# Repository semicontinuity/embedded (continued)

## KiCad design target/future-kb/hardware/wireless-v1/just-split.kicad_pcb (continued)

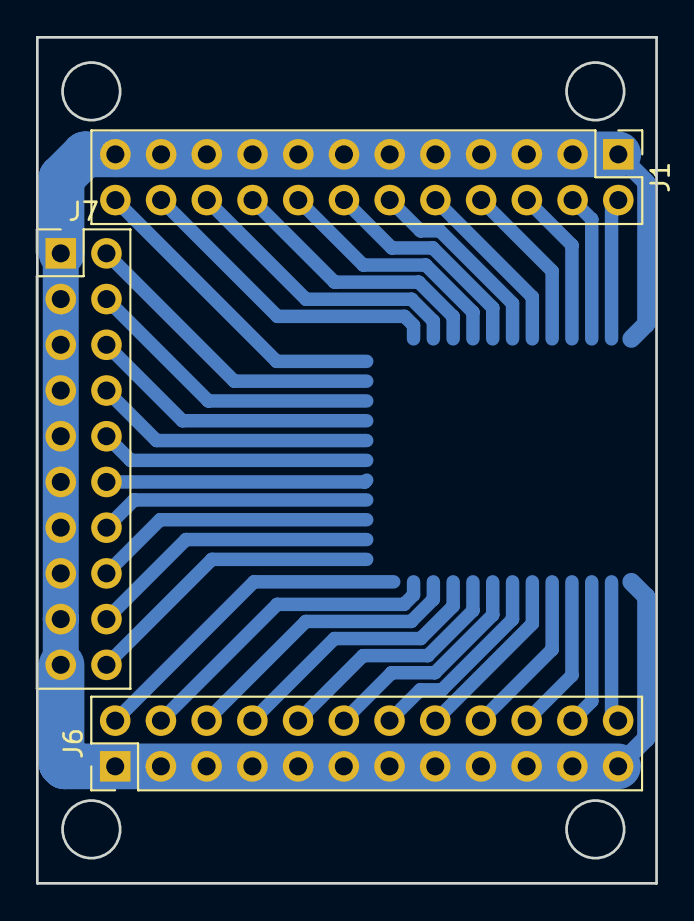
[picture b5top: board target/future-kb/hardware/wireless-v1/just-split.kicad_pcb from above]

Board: 2 copper layers, 34.4 x 47.0 mm, 4 parts (1 on the bottom side), 35 nets.

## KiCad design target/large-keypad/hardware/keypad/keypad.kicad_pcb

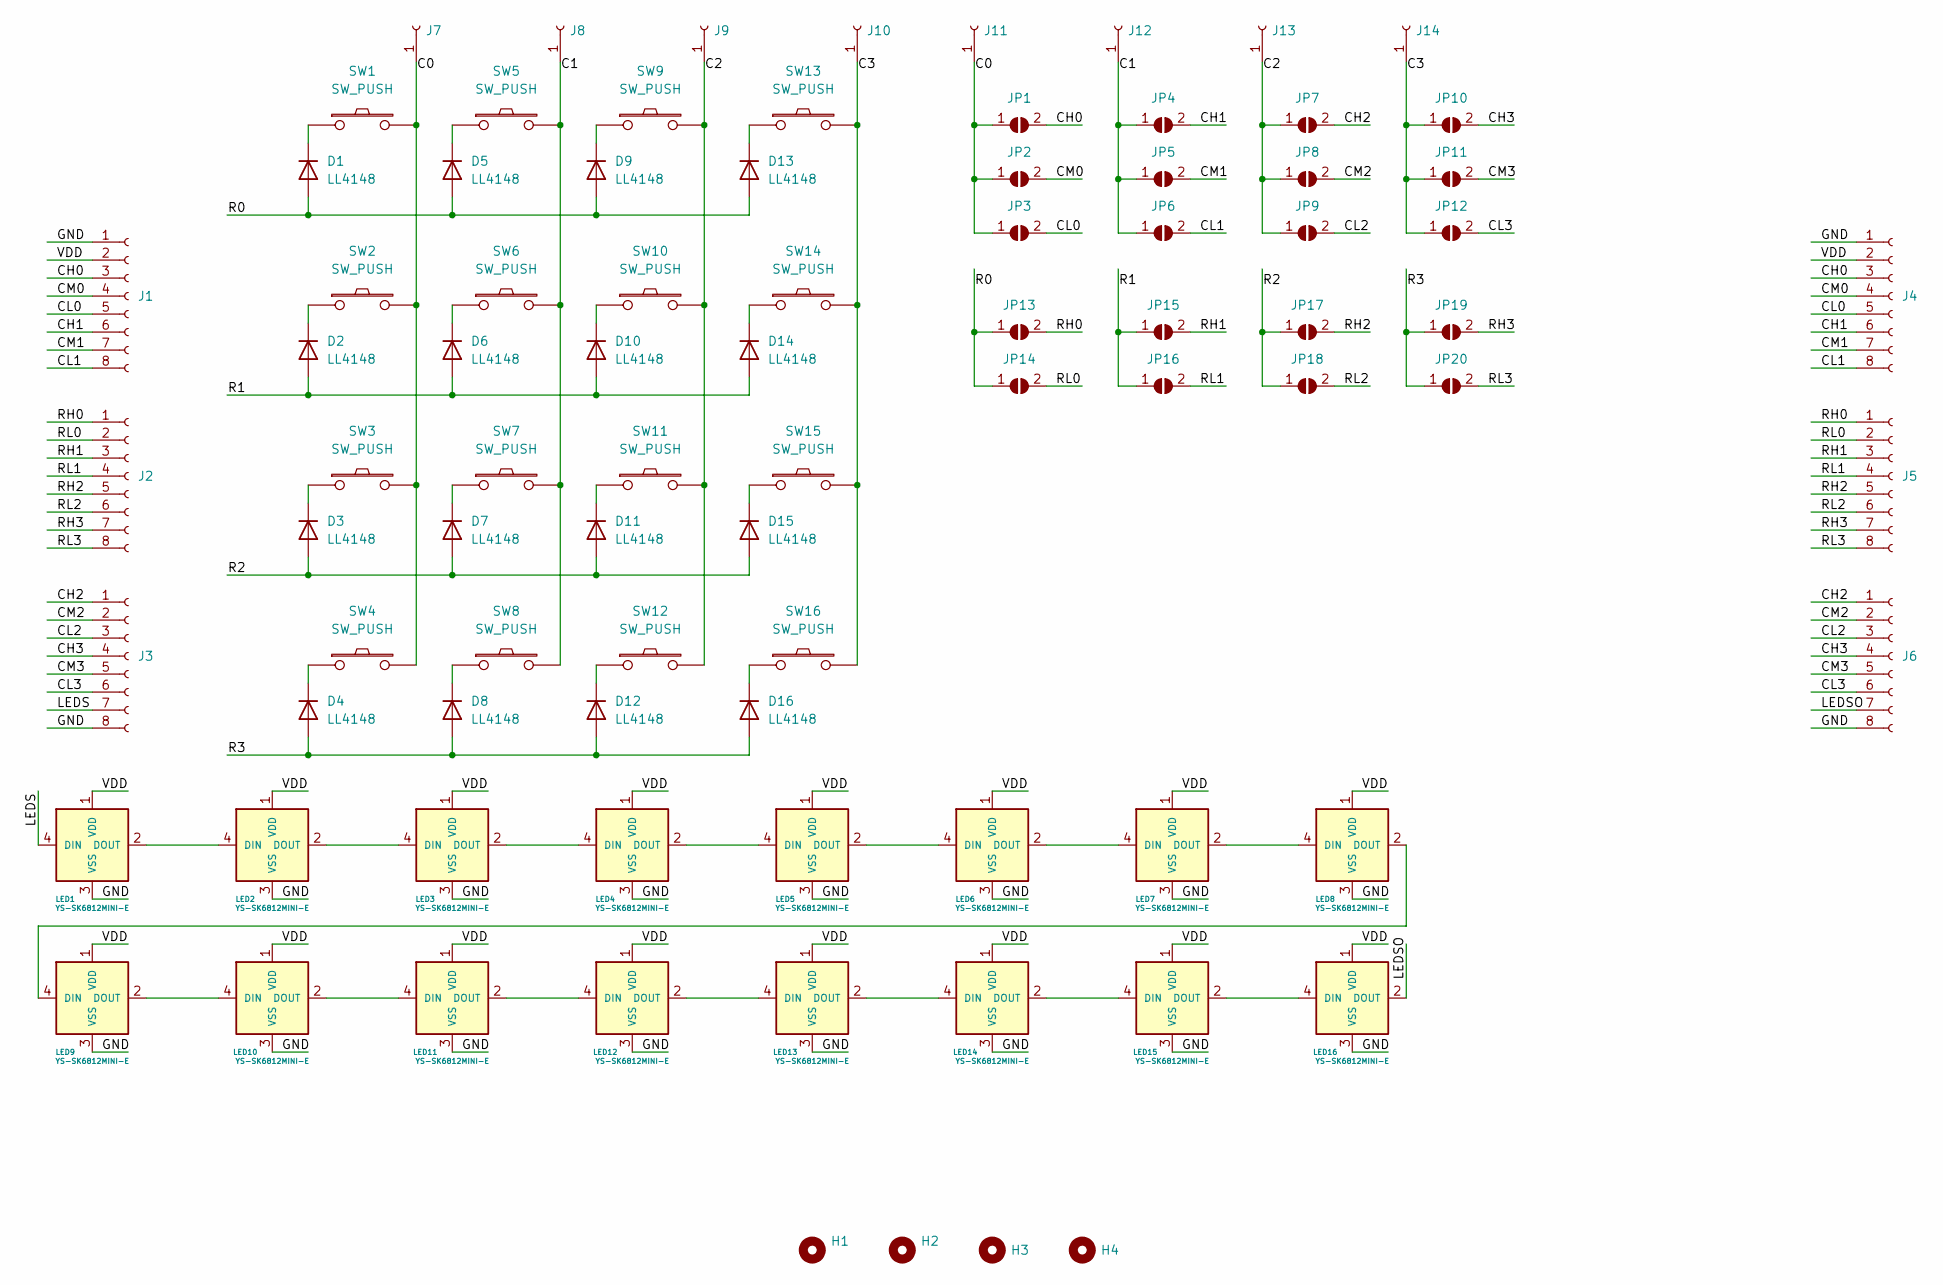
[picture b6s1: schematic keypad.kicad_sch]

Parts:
D1, D2, D3, D4, D5, D6, D7, D8, D9, D10, D11, D12, D13, D14, D15, D16: LL4148; D_MiniMELF
H1, H2, H3, H4: MountingHole; MountingHole_3.2mm_M3_ISO7380
J1, J2, J3: Conn_01x08_Female; PinSocket_1x08_P2.54mm_Horizontal
J4, J5, J6: Conn_01x08_Female; PinHeader_1x08_P2.54mm_Horizontal
J7, J8, J9, J10: Conn_01x01_Female; PinSocket_1x01_P2.54mm_Horizontal
J11, J12, J13, J14: Conn_01x01_Female; PinHeader_1x01_P2.54mm_Horizontal
JP1, JP2, JP3, JP4, JP5, JP6, JP7, JP8, JP9, JP10, JP11, JP12, JP13, JP14, JP15, JP16, JP17, JP18, JP19, JP20: SolderJumper_2_Open; Jumper
LED1, LED2, LED3, LED4, LED5, LED6, LED7, LED8, LED9, LED10, LED11, LED12, LED13, LED14, LED15, LED16: YS-SK6812MINI-E
SW1, SW2, SW3, SW4, SW5, SW6, SW7, SW8, SW9, SW10, SW11, SW12, SW13, SW14, SW15, SW16: SW_PUSH; CherryMX_Hotswap

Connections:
/C0: J7.1, J11.1, JP1.1 (A), JP2.1 (A), JP3.1 (A), SW1.2, SW2.2, SW3.2, SW4.2
/C1: J8.1, J12.1, JP4.1 (A), JP5.1 (A), JP6.1 (A), SW5.2, SW6.2, SW7.2, SW8.2
/C2: J9.1, J13.1, JP7.1 (A), JP8.1 (A), JP9.1 (A), SW9.2, SW10.2, SW11.2, SW12.2
/C3: J10.1, J14.1, JP10.1 (A), JP11.1 (A), JP12.1 (A), SW13.2, SW14.2, SW15.2, SW16.2
/CH0: J1.3, J4.3, JP1.2 (B)
/CH1: J1.6, J4.6, JP4.2 (B)
/CH2: J3.1, J6.1, JP7.2 (B)
/CH3: J3.4, J6.4, JP10.2 (B)
/CL0: J1.5, J4.5, JP3.2 (B)
/CL1: J1.8, J4.8, JP6.2 (B)
/CL2: J3.3, J6.3, JP9.2 (B)
/CL3: J3.6, J6.6, JP12.2 (B)
/CM0: J1.4, J4.4, JP2.2 (B)
/CM1: J1.7, J4.7, JP5.2 (B)
/CM2: J3.2, J6.2, JP8.2 (B)
/CM3: J3.5, J6.5, JP11.2 (B)
/GND: J1.1, J3.8, J4.1, J6.8, LED1.3 (VSS), LED2.3 (VSS), LED3.3 (VSS), LED4.3 (VSS), LED5.3 (VSS), LED6.3 (VSS), LED7.3 (VSS), LED8.3 (VSS), LED9.3 (VSS), LED10.3 (VSS), LED11.3 (VSS), LED12.3 (VSS), LED13.3 (VSS), LED14.3 (VSS), LED15.3 (VSS), LED16.3 (VSS)
/LEDS: J3.7, LED1.4 (DIN)
/LEDSO: J6.7, LED16.2 (DOUT)
/R0: D1.2 (A), D5.2 (A), D9.2 (A), D13.2 (A), JP13.1 (A), JP14.1 (A)
/R1: D2.2 (A), D6.2 (A), D10.2 (A), D14.2 (A), JP15.1 (A), JP16.1 (A)
/R2: D3.2 (A), D7.2 (A), D11.2 (A), D15.2 (A), JP17.1 (A), JP18.1 (A)
/R3: D4.2 (A), D8.2 (A), D12.2 (A), D16.2 (A), JP19.1 (A), JP20.1 (A)
/RH0: J2.1, J5.1, JP13.2 (B)
/RH1: J2.3, J5.3, JP15.2 (B)
/RH2: J2.5, J5.5, JP17.2 (B)
/RH3: J2.7, J5.7, JP19.2 (B)
/RL0: J2.2, J5.2, JP14.2 (B)
/RL1: J2.4, J5.4, JP16.2 (B)
/RL2: J2.6, J5.6, JP18.2 (B)
/RL3: J2.8, J5.8, JP20.2 (B)
/VDD: J1.2, J4.2, LED1.1 (VDD), LED2.1 (VDD), LED3.1 (VDD), LED4.1 (VDD), LED5.1 (VDD), LED6.1 (VDD), LED7.1 (VDD), LED8.1 (VDD), LED9.1 (VDD), LED10.1 (VDD), LED11.1 (VDD), LED12.1 (VDD), LED13.1 (VDD), LED14.1 (VDD), LED15.1 (VDD), LED16.1 (VDD)
unnamed: D1.1 (K), SW1.1
unnamed: D2.1 (K), SW2.1
unnamed: D3.1 (K), SW3.1
unnamed: D4.1 (K), SW4.1
unnamed: D5.1 (K), SW5.1
unnamed: D6.1 (K), SW6.1
unnamed: D7.1 (K), SW7.1
unnamed: D8.1 (K), SW8.1
unnamed: D9.1 (K), SW9.1
unnamed: D10.1 (K), SW10.1
unnamed: D11.1 (K), SW11.1
unnamed: D12.1 (K), SW12.1
unnamed: D13.1 (K), SW13.1
unnamed: D14.1 (K), SW14.1
unnamed: D15.1 (K), SW15.1
unnamed: D16.1 (K), SW16.1
unnamed: LED1.2 (DOUT), LED2.4 (DIN)
unnamed: LED2.2 (DOUT), LED3.4 (DIN)
unnamed: LED3.2 (DOUT), LED4.4 (DIN)
unnamed: LED4.2 (DOUT), LED5.4 (DIN)
unnamed: LED5.2 (DOUT), LED6.4 (DIN)
unnamed: LED6.2 (DOUT), LED7.4 (DIN)
unnamed: LED7.2 (DOUT), LED8.4 (DIN)
unnamed: LED8.2 (DOUT), LED9.4 (DIN)
unnamed: LED10.2 (DOUT), LED11.4 (DIN)
unnamed: LED9.2 (DOUT), LED10.4 (DIN)
unnamed: LED11.2 (DOUT), LED12.4 (DIN)
unnamed: LED12.2 (DOUT), LED13.4 (DIN)
unnamed: LED13.2 (DOUT), LED14.4 (DIN)
unnamed: LED14.2 (DOUT), LED15.4 (DIN)
unnamed: LED15.2 (DOUT), LED16.4 (DIN)

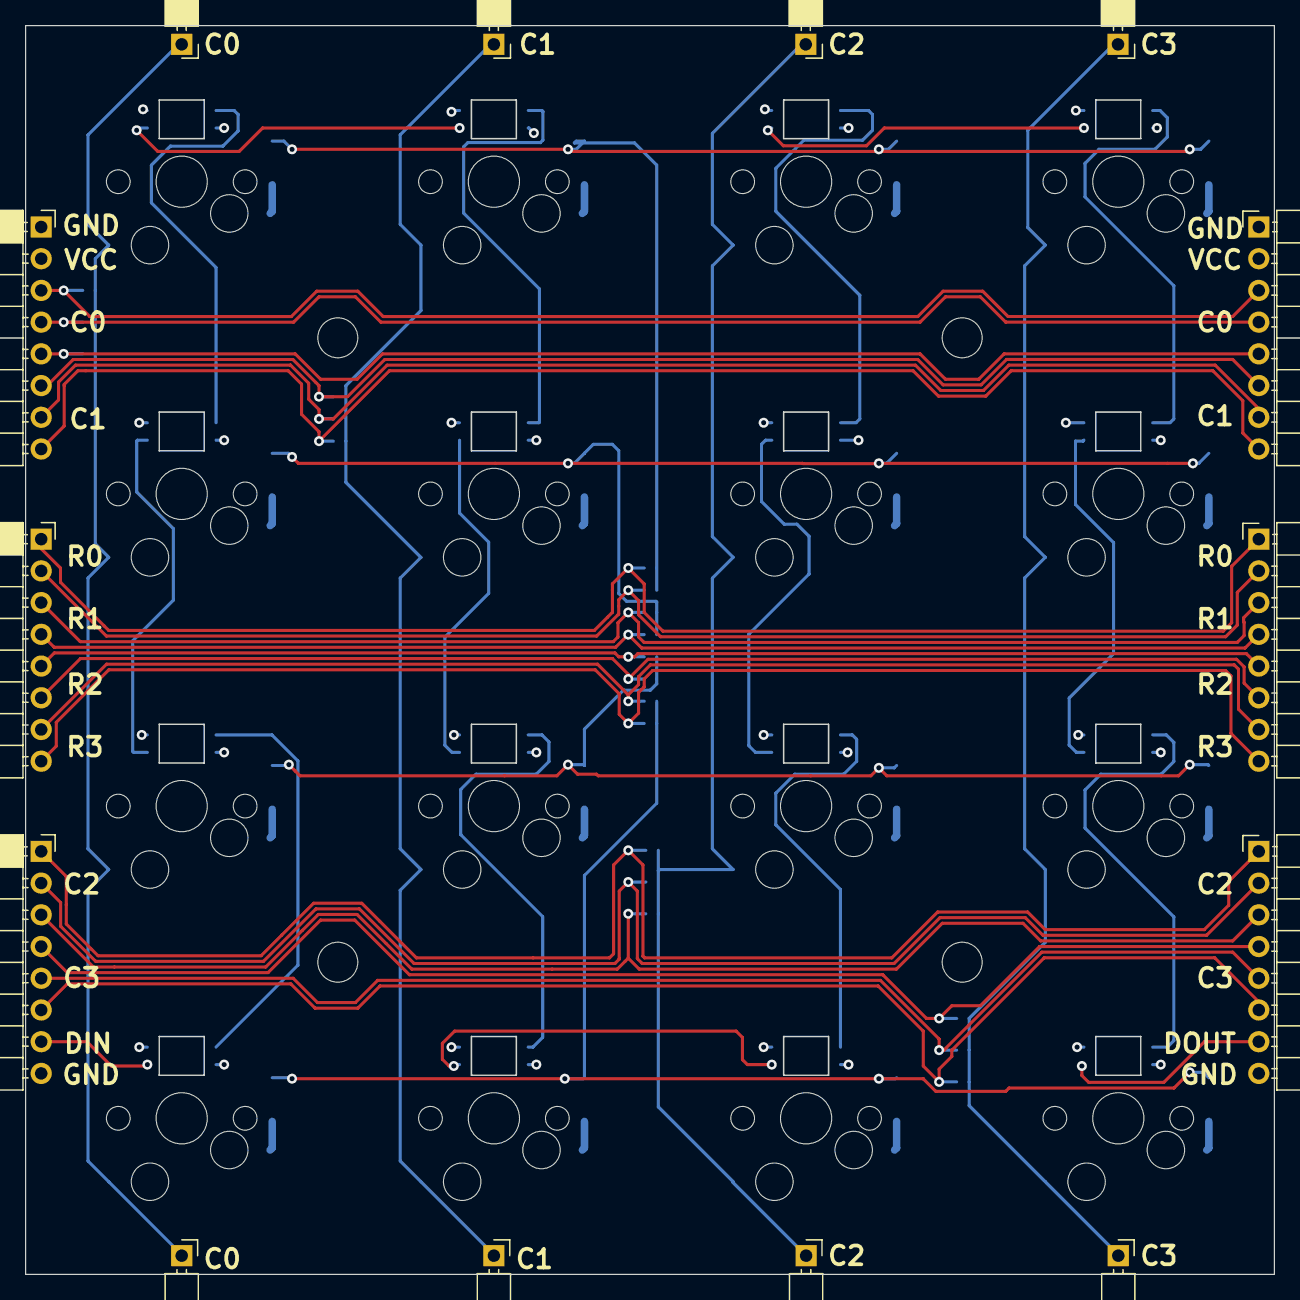
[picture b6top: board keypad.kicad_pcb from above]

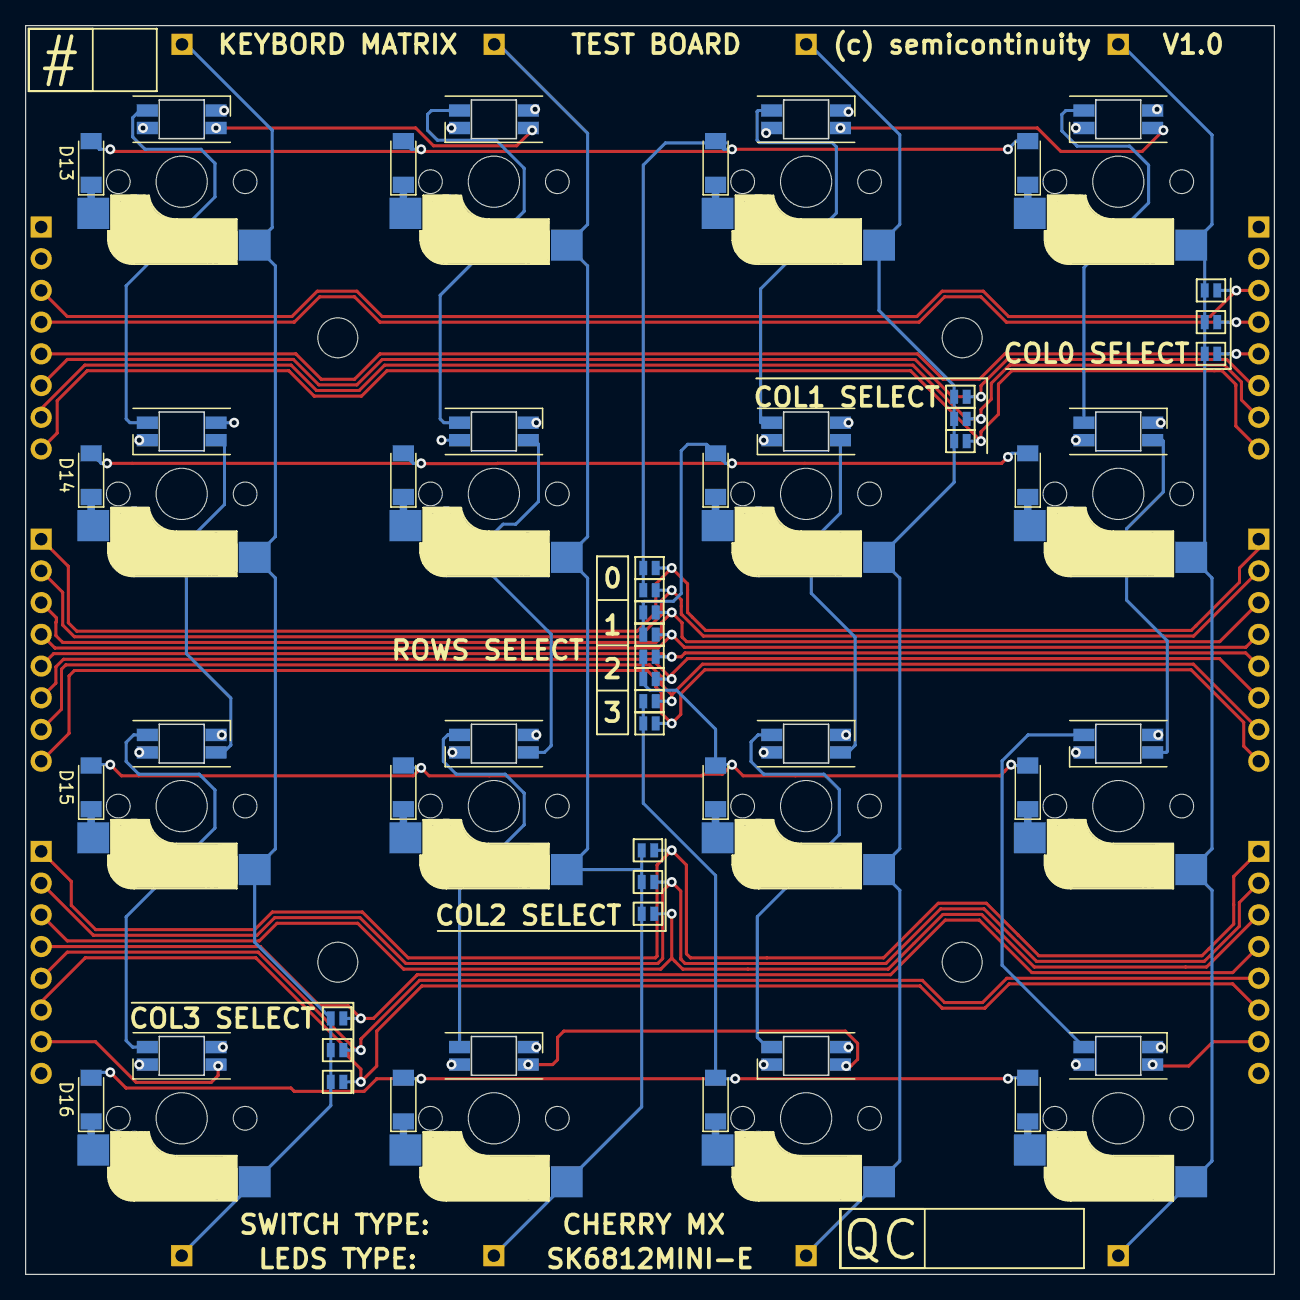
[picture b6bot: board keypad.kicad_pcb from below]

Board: 4 copper layers, 100.0 x 100.0 mm, 86 parts (52 on the bottom side), 63 nets.

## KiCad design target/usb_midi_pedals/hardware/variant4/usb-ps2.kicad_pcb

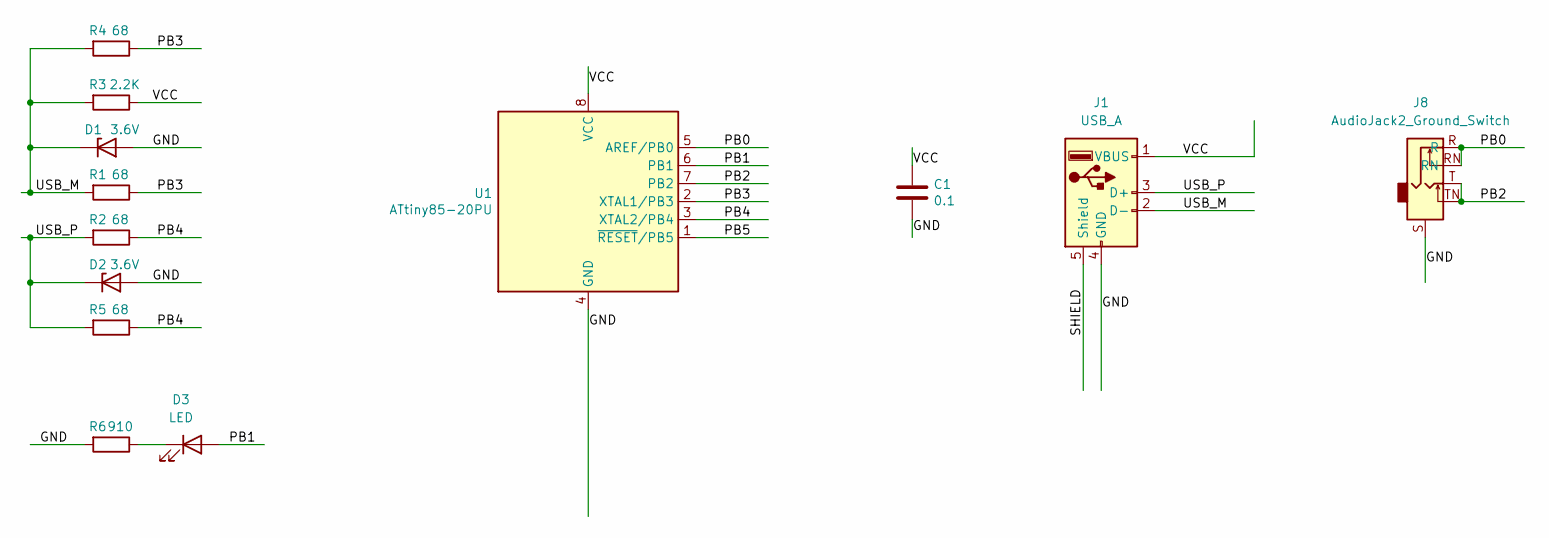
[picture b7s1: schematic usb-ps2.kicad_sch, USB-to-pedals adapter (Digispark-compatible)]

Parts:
C1: 0.1; C_0805_2012Metric_Pad1.18x1.45mm_HandSolder
D1, D2: 3.6V; D_DO-35_SOD27_P5.08mm_Vertical_AnodeUp
D3: LED; LED_0805_2012Metric_Pad1.15x1.40mm_HandSolder
J1: USB_A; USB_A_CONNFLY_DS1095-WNR0
J8: AudioJack2_Ground_Switch; Jack_3.5mm_CUI_SJ1-3525N_Horizontal
R1, R2: 68; R_Axial_DIN0204_L3.6mm_D1.6mm_P5.08mm_Horizontal
R3: 2.2K; R_0805_2012Metric_Pad1.20x1.40mm_HandSolder
R4, R5: 68; R_0805_2012Metric_Pad1.20x1.40mm_HandSolder
R6: 910; R_0805_2012Metric_Pad1.20x1.40mm_HandSolder
U1: ATtiny85-20PU; DIP-8_W7.62mm

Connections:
/GND: C1.2, D1.2 (A), D2.2 (A), J1.4 (GND), J8.S, R6.2, U1.4 (GND)
/PB0: J8.R, J8.RN, U1.5 (AREF/PB0)
/PB1: D3.2 (A), U1.6 (PB1)
/PB2: J8.T, J8.TN, U1.7 (PB2)
/PB3: R1.1, R4.1, U1.2 (XTAL1/PB3)
/PB4: R2.1, R5.1, U1.3 (XTAL2/PB4)
/PB5: U1.1 (~RESET/PB5)
/SHIELD: J1.5 (Shield)
/USB_M: D1.1 (K), J1.2 (D-), R1.2, R3.2, R4.2
/USB_P: D2.1 (K), J1.3 (D+), R2.2, R5.2
/VCC: C1.1, J1.1 (VBUS), R3.1, U1.8 (VCC)
unnamed: D3.1 (K), R6.1

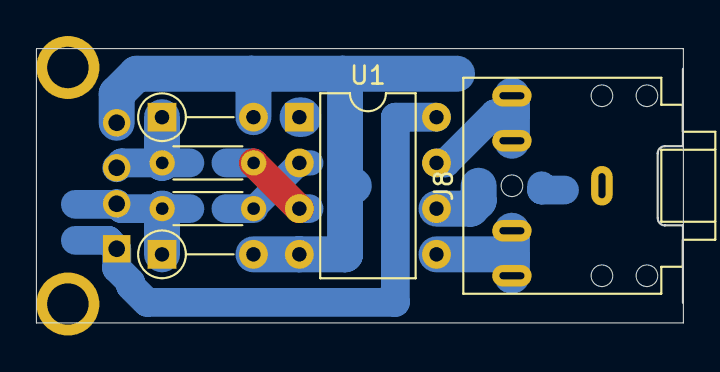
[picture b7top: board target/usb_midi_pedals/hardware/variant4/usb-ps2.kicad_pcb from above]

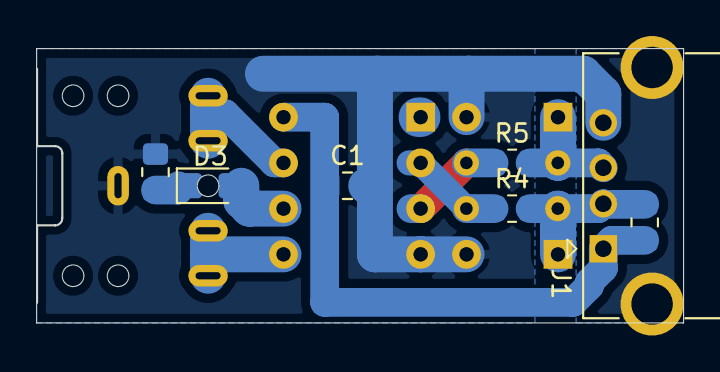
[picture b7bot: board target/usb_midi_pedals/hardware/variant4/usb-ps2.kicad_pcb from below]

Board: 2 copper layers, 35.9 x 15.2 mm, 13 parts (7 on the bottom side), 10 nets.

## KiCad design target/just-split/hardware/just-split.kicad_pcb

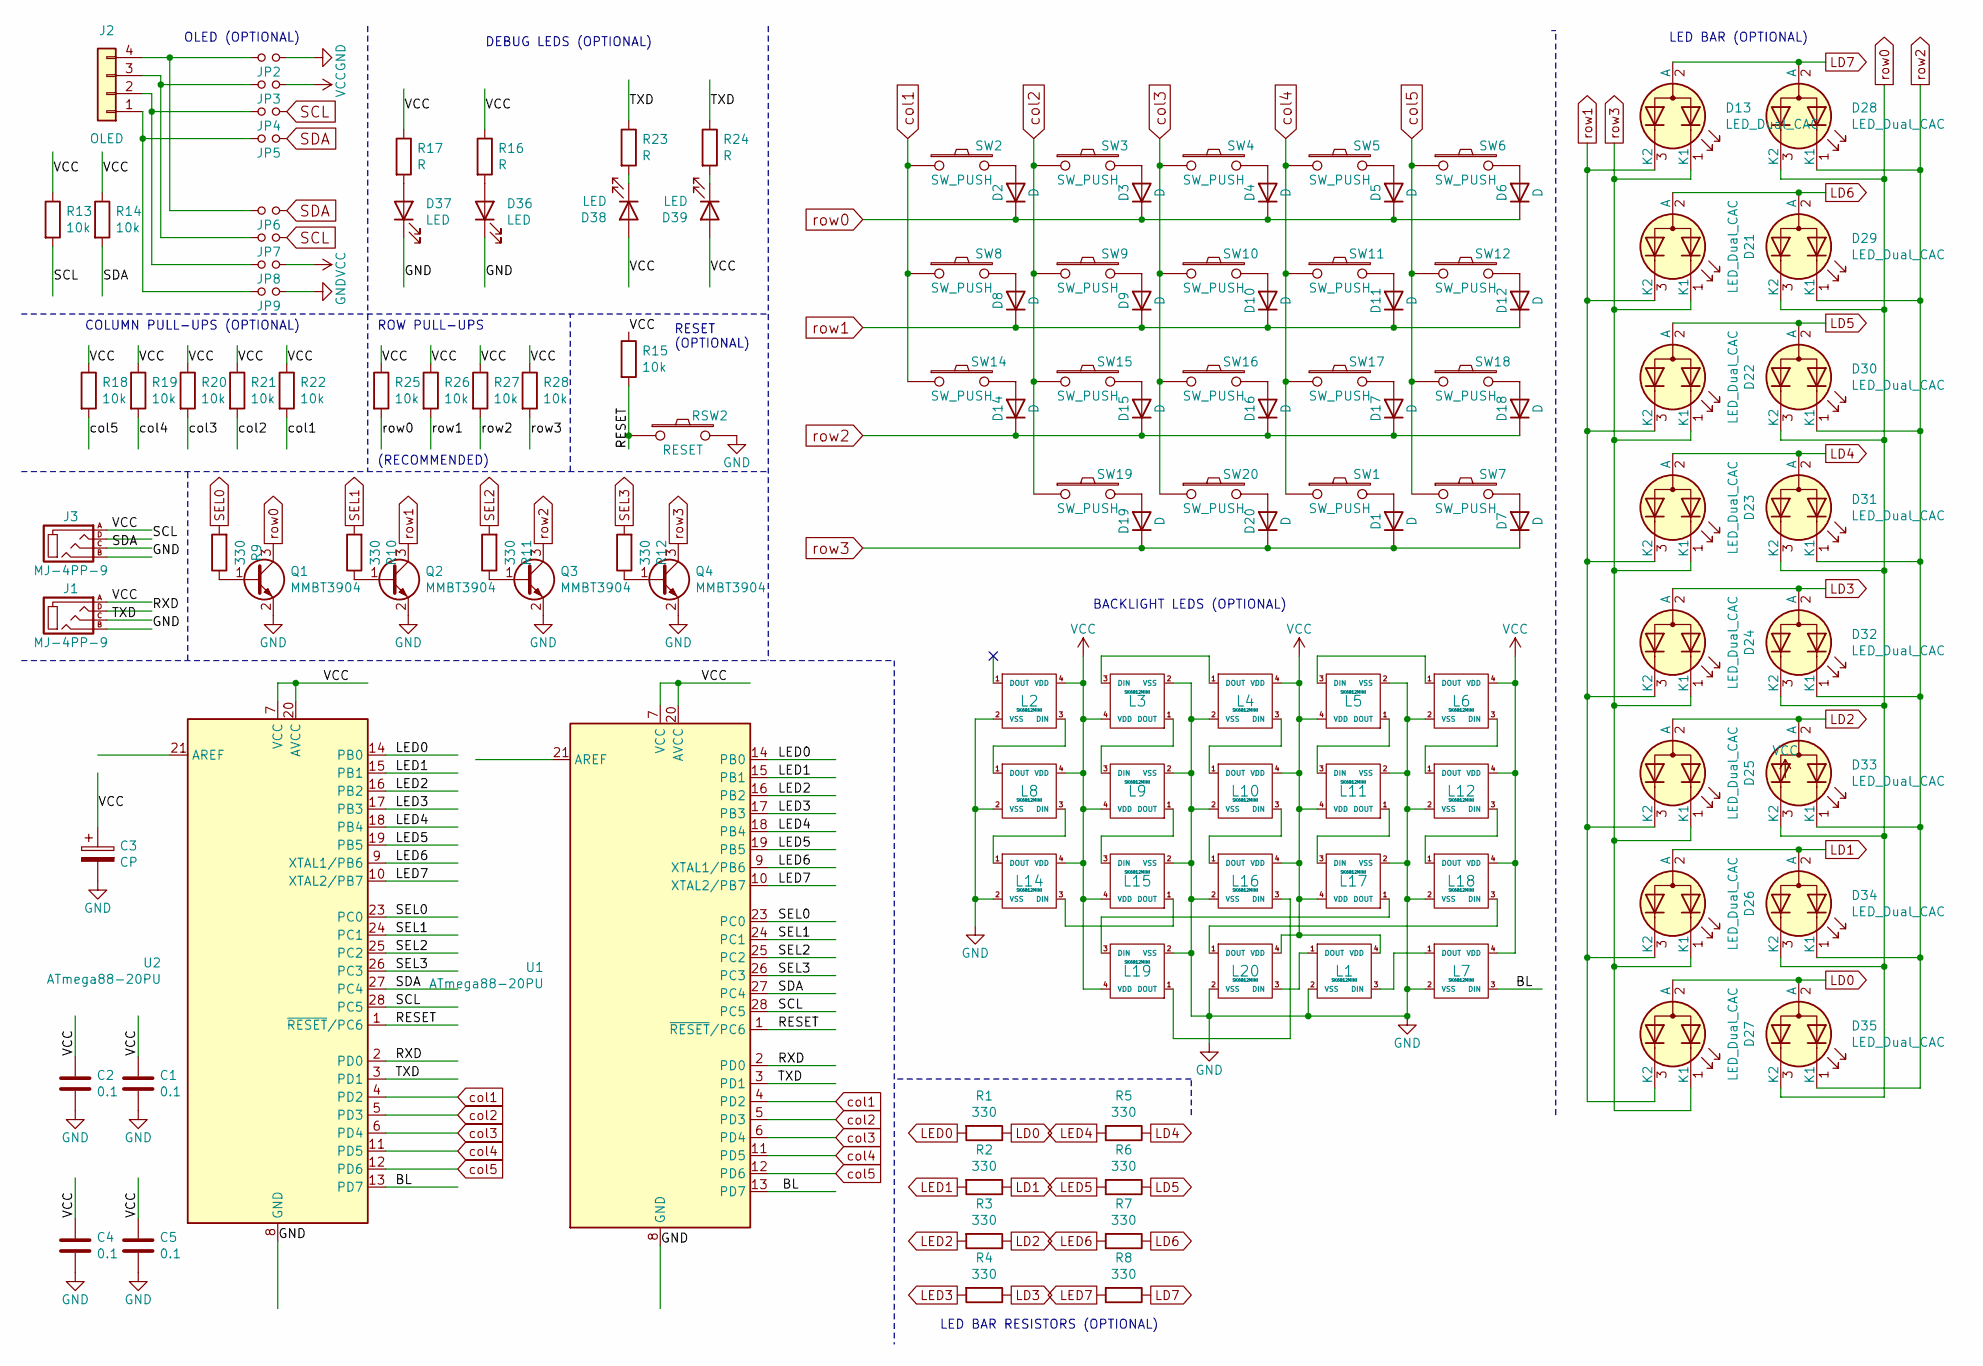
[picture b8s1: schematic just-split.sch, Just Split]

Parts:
C1, C2, C4, C5: 0.1; C_0805_2012Metric_Pad1.18x1.45mm_HandSolder
C3: CP; SolderWire-0.5sqmm_1x02_P4.6mm_D0.9mm_OD2.1mm
D1, D2, D3, D4, D5, D6, D7, D8, D9, D10, D11, D12, D14, D15, D16, D17, D18, D19, D20: D; D3_TH_SMD
D13, D21, D22, D23, D24, D25, D26, D27, D28, D29, D30, D31, D32, D33, D34, D35: LED_Dual_CAC; LED_Rectangular_W5.0mm_H2.0mm-3Pins
D36, D37, D38, D39: LED; LED_0805_2012Metric_Pad1.15x1.40mm_HandSolder
J1, J3: MJ-4PP-9
J2: OLED
JP2, JP3, JP4, JP5, JP6, JP7, JP8, JP9: Jumper
L1, L2, L3, L4, L5, L6, L7, L8, L9, L10, L11, L12, L14, L15, L16, L17, L18, L19, L20: SK6812MINI; SK6812MINI_rev
Q1, Q2, Q3, Q4: MMBT3904; SOT-23
R1, R2, R3, R4, R5, R6, R7, R8, R9, R10, R11, R12: 330; R_0805_2012Metric_Pad1.20x1.40mm_HandSolder
R13, R14, R15, R18, R19, R20, R21, R22: 10k; R_Axial_DIN0207_L6.3mm_D2.5mm_P7.62mm_Horizontal
R16, R17, R23, R24: R; R_0805_2012Metric_Pad1.20x1.40mm_HandSolder
R25, R26, R27, R28: 10k; R_0805_2012Metric_Pad1.20x1.40mm_HandSolder
RSW2: RESET; ResetSW
SW1, SW2, SW3, SW4, SW5, SW6, SW7, SW8, SW9, SW10, SW11, SW12, SW14, SW15, SW16, SW17, SW18, SW19, SW20: SW_PUSH; MX_ALPS_PG1350_noLed
U1, U2: ATmega88-20PU; DIP-28_W7.62mm

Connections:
/BL: L7.3 (DIN), U1.13 (PD7), U2.13 (PD7)
/RESET: R15.2, RSW2.1, U1.1 (~RESET~/PC6), U2.1 (~RESET~/PC6)
/RXD: J1.D, U1.2 (PD0), U2.2 (PD0)
/TXD: J1.C, R23.1, R24.1, U1.3 (PD1), U2.3 (PD1)
GND: C1.2, C2.2, C3.2, C4.2, C5.2, D36.1 (K), D37.1 (K), J1.B, J3.B, JP2.1, JP9.1, L1.2 (VSS), L2.2 (VSS), L3.2 (VSS), L4.2 (VSS), L5.2 (VSS), L6.2 (VSS), L7.2 (VSS), L8.2 (VSS), L9.2 (VSS), L10.2 (VSS), L11.2 (VSS), L12.2 (VSS), L14.2 (VSS), L15.2 (VSS), L16.2 (VSS), L17.2 (VSS), L18.2 (VSS), L19.2 (VSS), L20.2 (VSS), Q1.2 (E), Q2.2 (E), Q3.2 (E), Q4.2 (E), RSW2.2, U1.8 (GND), U1.22 (GND), U2.8 (GND), U2.22 (GND)
LD0: D27.2 (A), D35.2 (A), R1.1
LD1: D26.2 (A), D34.2 (A), R2.1
LD2: D25.2 (A), D33.2 (A), R3.1
LD3: D24.2 (A), D32.2 (A), R4.1
LD4: D23.2 (A), D31.2 (A), R5.1
LD5: D22.2 (A), D30.2 (A), R6.1
LD6: D21.2 (A), D29.2 (A), R7.1
LD7: D13.2 (A), D28.2 (A), R8.1
LED0: R1.2, U1.14 (PB0), U2.14 (PB0)
LED1: R2.2, U1.15 (PB1), U2.15 (PB1)
LED2: R3.2, U1.16 (PB2), U2.16 (PB2)
LED3: R4.2, U1.17 (PB3), U2.17 (PB3)
LED4: R5.2, U1.18 (PB4), U2.18 (PB4)
LED5: R6.2, U1.19 (PB5), U2.19 (PB5)
LED6: R7.2, U1.9 (XTAL1/PB6), U2.9 (XTAL1/PB6)
LED7: R8.2, U1.10 (XTAL2/PB7), U2.10 (XTAL2/PB7)
unnamed: D1.2 (A), SW1.2
unnamed: D2.2 (A), SW2.2
unnamed: D3.2 (A), SW3.2
unnamed: D4.2 (A), SW4.2
unnamed: D5.2 (A), SW5.2
unnamed: D6.2 (A), SW6.2
unnamed: D7.2 (A), SW7.2
unnamed: D8.2 (A), SW8.2
unnamed: D9.2 (A), SW9.2
unnamed: D10.2 (A), SW10.2
unnamed: D11.2 (A), SW11.2
unnamed: D12.2 (A), SW12.2
unnamed: D14.2 (A), SW14.2
unnamed: D15.2 (A), SW15.2
unnamed: D16.2 (A), SW16.2
unnamed: D17.2 (A), SW17.2
unnamed: D18.2 (A), SW18.2
unnamed: D19.2 (A), SW19.2
unnamed: D20.2 (A), SW20.2
unnamed: D36.2 (A), R16.2
unnamed: D37.2 (A), R17.2
unnamed: D38.1 (K), R23.2
unnamed: D39.1 (K), R24.2
unnamed: J2.1, JP5.2, JP9.2
unnamed: J2.2, JP4.2, JP8.2
unnamed: J2.3, JP3.2, JP7.2
unnamed: J2.4, JP2.2, JP6.2
unnamed: L1.1 (DOUT), L20.3 (DIN)
unnamed: L1.3 (DIN), L7.1 (DOUT)
unnamed: L2.3 (DIN), L8.1 (DOUT)
unnamed: L3.1 (DOUT), L9.3 (DIN)
unnamed: L3.3 (DIN), L4.1 (DOUT)
unnamed: L5.3 (DIN), L6.1 (DOUT)
unnamed: L4.3 (DIN), L10.1 (DOUT)
unnamed: L10.3 (DIN), L16.1 (DOUT)
unnamed: L11.1 (DOUT), L17.3 (DIN)
unnamed: L5.1 (DOUT), L11.3 (DIN)
unnamed: L6.3 (DIN), L12.1 (DOUT)
unnamed: L12.3 (DIN), L18.1 (DOUT)
unnamed: L8.3 (DIN), L14.1 (DOUT)
unnamed: L14.3 (DIN), L15.1 (DOUT)
unnamed: L9.1 (DOUT), L15.3 (DIN)
unnamed: L16.3 (DIN), L19.1 (DOUT)
unnamed: L17.1 (DOUT), L19.3 (DIN)
unnamed: L18.3 (DIN), L20.1 (DOUT)
unnamed: Q1.1 (B), R9.1
unnamed: Q2.1 (B), R10.1
unnamed: Q3.1 (B), R11.1
unnamed: Q4.1 (B), R12.1
SCL: J3.D, JP4.1, JP7.1, R13.2, U1.28 (PC5), U2.28 (PC5)
SDA: J3.C, JP5.1, JP6.1, R14.2, U1.27 (PC4), U2.27 (PC4)
SEL0: R9.2, U1.23 (PC0), U2.23 (PC0)
SEL1: R10.2, U1.24 (PC1), U2.24 (PC1)
SEL2: R11.2, U1.25 (PC2), U2.25 (PC2)
SEL3: R12.2, U1.26 (PC3), U2.26 (PC3)
VCC: C1.1, C2.1, C3.1, C4.1, C5.1, D38.2 (A), D39.2 (A), J1.A, J3.A, JP3.1, JP8.1, L1.4 (VDD), L2.4 (VDD), L3.4 (VDD), L4.4 (VDD), L5.4 (VDD), L6.4 (VDD), L7.4 (VDD), L8.4 (VDD), L9.4 (VDD), L10.4 (VDD), L11.4 (VDD), L12.4 (VDD), L14.4 (VDD), L15.4 (VDD), L16.4 (VDD), L17.4 (VDD), L18.4 (VDD), L19.4 (VDD), L20.4 (VDD), R13.1, R14.1, R15.1, R16.1, R17.1, R18.1, R19.1, R20.1, R21.1, R22.1, R25.1, R26.1, R27.1, R28.1, U1.7 (VCC), U1.20 (AVCC), U2.7 (VCC), U2.20 (AVCC)
col1: R22.2, SW2.1, SW8.1, SW14.1, U1.4 (PD2), U2.4 (PD2)
col2: R21.2, SW3.1, SW9.1, SW15.1, SW19.1, U1.5 (PD3), U2.5 (PD3)
col3: R20.2, SW4.1, SW10.1, SW16.1, SW20.1, U1.6 (PD4), U2.6 (PD4)
col4: R19.2, SW1.1, SW5.1, SW11.1, SW17.1, U1.11 (PD5), U2.11 (PD5)
col5: R18.2, SW6.1, SW7.1, SW12.1, SW18.1, U1.12 (PD6), U2.12 (PD6)
row0: D2.1 (K), D3.1 (K), D4.1 (K), D5.1 (K), D6.1 (K), D28.3 (K2), D29.3 (K2), D30.3 (K2), D31.3 (K2), D32.3 (K2), D33.3 (K2), D34.3 (K2), D35.3 (K2), Q1.3 (C), R25.2
row1: D8.1 (K), D9.1 (K), D10.1 (K), D11.1 (K), D12.1 (K), D13.3 (K2), D21.3 (K2), D22.3 (K2), D23.3 (K2), D24.3 (K2), D25.3 (K2), D26.3 (K2), D27.3 (K2), Q2.3 (C), R26.2
row2: D14.1 (K), D15.1 (K), D16.1 (K), D17.1 (K), D18.1 (K), D28.1 (K1), D29.1 (K1), D30.1 (K1), D31.1 (K1), D32.1 (K1), D33.1 (K1), D34.1 (K1), D35.1 (K1), Q3.3 (C), R27.2
row3: D1.1 (K), D7.1 (K), D13.1 (K1), D19.1 (K), D20.1 (K), D21.1 (K1), D22.1 (K1), D23.1 (K1), D24.1 (K1), D25.1 (K1), D26.1 (K1), D27.1 (K1), Q4.3 (C), R28.2

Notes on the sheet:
COLUMN PULL-UPS (OPTIONAL)
RESET (OPTIONAL)
DEBUG LEDS (OPTIONAL)
OLED (OPTIONAL)
LED BAR RESISTORS (OPTIONAL)
BACKLIGHT LEDS (OPTIONAL)
LED BAR (OPTIONAL)
ROW PULL-UPS
(RECOMMENDED)

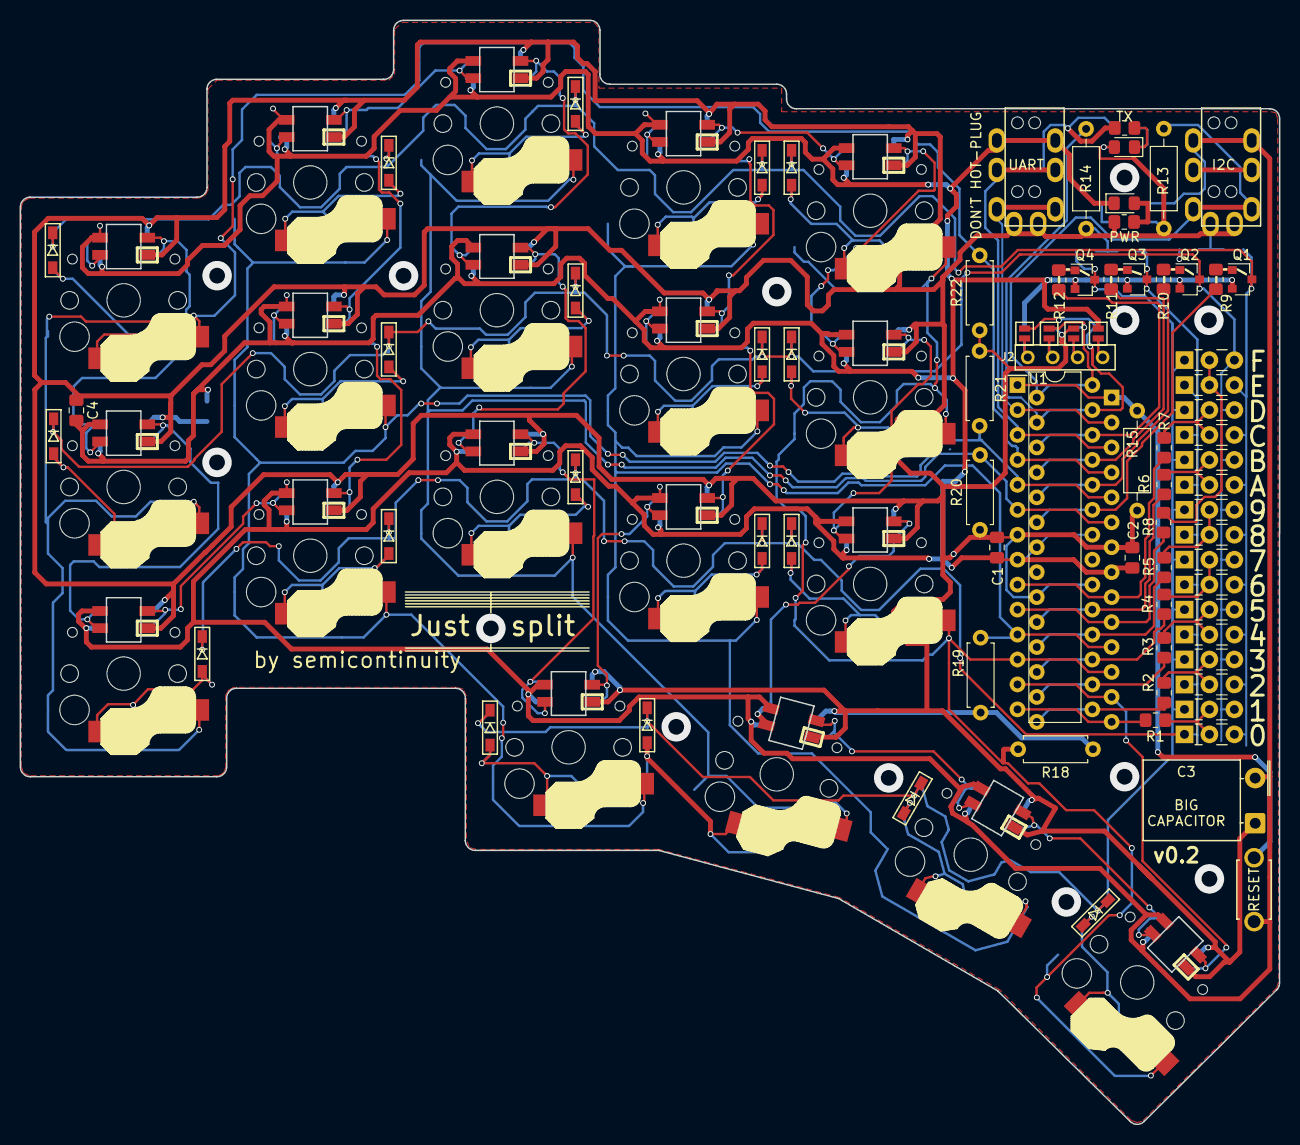
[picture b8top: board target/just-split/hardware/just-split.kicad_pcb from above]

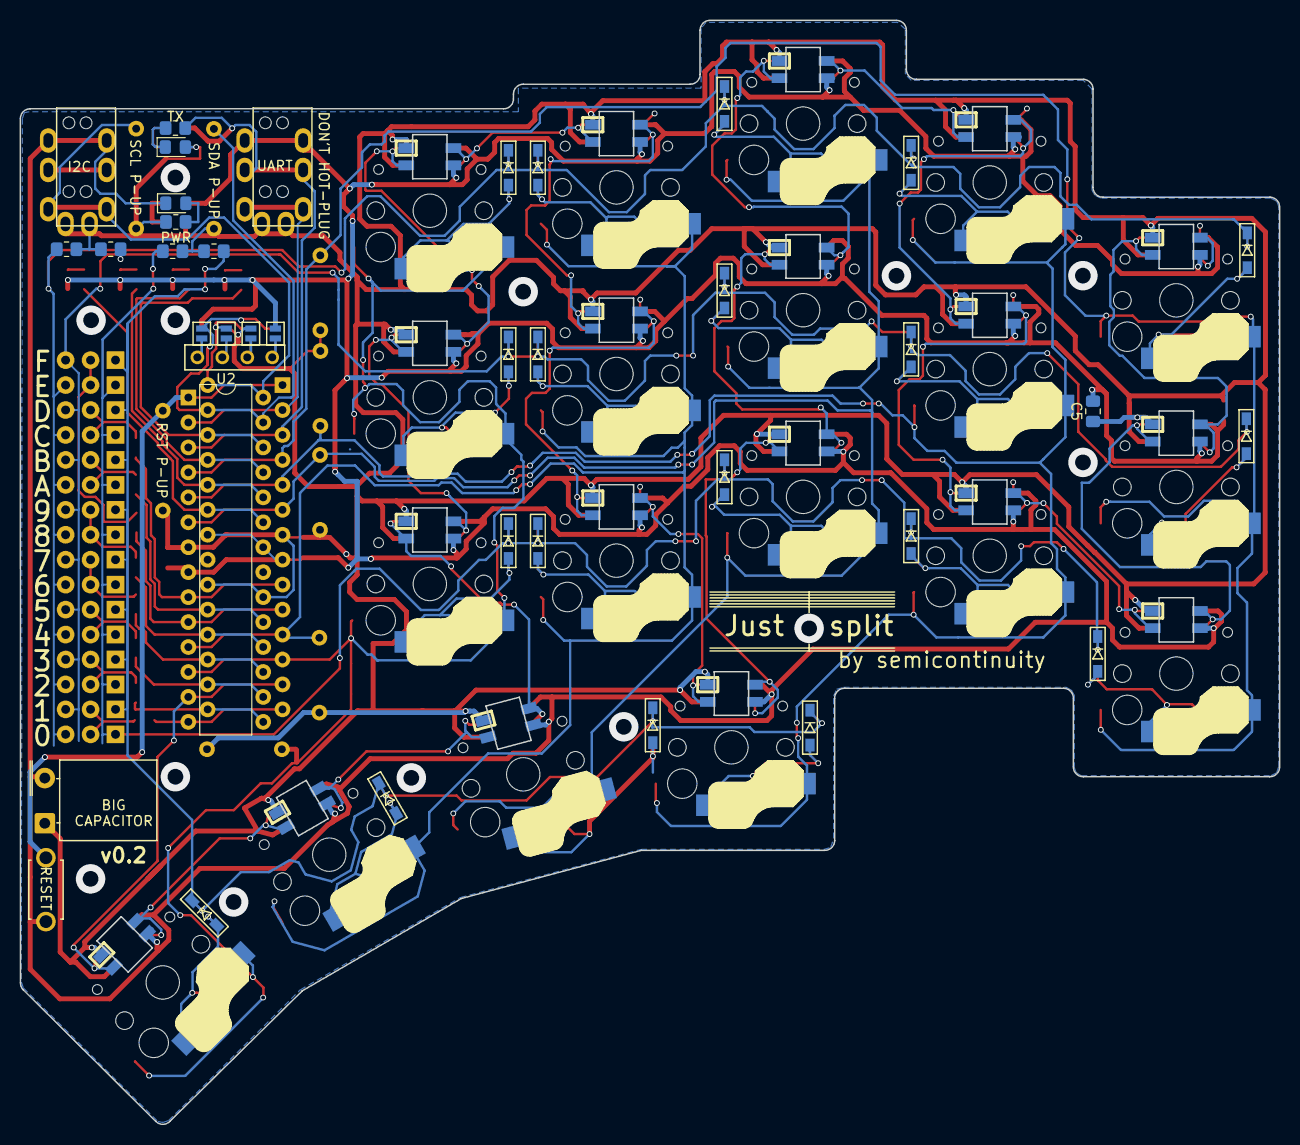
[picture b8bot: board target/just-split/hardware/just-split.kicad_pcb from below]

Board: 2 copper layers, 128.2 x 112.4 mm, 128 parts (14 on the bottom side), 86 nets.
